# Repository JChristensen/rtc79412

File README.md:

# MCP78411/12 RTC Break-Out Board
https://github.com/JChristensen/rtc79412  
README file  
Jack Christensen  
Sep-2012

## License
  
This work is licensed under the [Creative Commons Attribution-ShareAlike 4.0 International License](https://creativecommons.org/licenses/by-sa/4.0/).

## Introduction
Break-out board for the Microchip MCP78411/12 Real-Time Clock.  

For an Arduino library that supports the MCP79412 RTC, see:
https://github.com/JChristensen/MCP79412RTC

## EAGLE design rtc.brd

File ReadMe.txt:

ReadMe file for MCP79412 Real-Time Clock Breakout Board v1.0
https://github.com/JChristensen/rtc79412
Jack Christensen Sep 2012

This work is licensed under the Creative Commons Attribution-ShareAlike 3.0
Unported License. To view a copy of this license, visit
http://creativecommons.org/licenses/by-sa/3.0/ or send a letter to Creative
Commons, 171 Second Street, Suite 300, San Francisco, California, 94105, USA.

================================================================================
This repository contains the following for the MCP79412 Real-Time Clock Breakout
Board:

Schematic
Eagle Files
Bill of materials (below)

For an Arduino library that supports the MCP79412 RTC, see:
https://github.com/JChristensen/MCP79412RTC

================================================================================
MCP79412 RTC Breakout Board
Bill of Materials

Part   Value                   Package   Comments
----   ---------------------   -------   ---------------------------------
B1     CR2016 battery holder             Linx Technologies BAT-HLD-002-SMT
C1     100nF                   C0805
C2     100pF                   C0805
C3     10pF                    C0805
C4     8.2pF                   C0805
D1     PMEG6002EJ              SOD323    NXP Low Vf Schottky Diode
R1     10K                     R0805
R2     2.2K                    R0805
R3     2.2K                    R0805
R4     1K                      R0805
U1     MCP79412-I/SN           SO08
Y1     32.768 kHz                        Citizen CM200C-32.768KDZB-UT

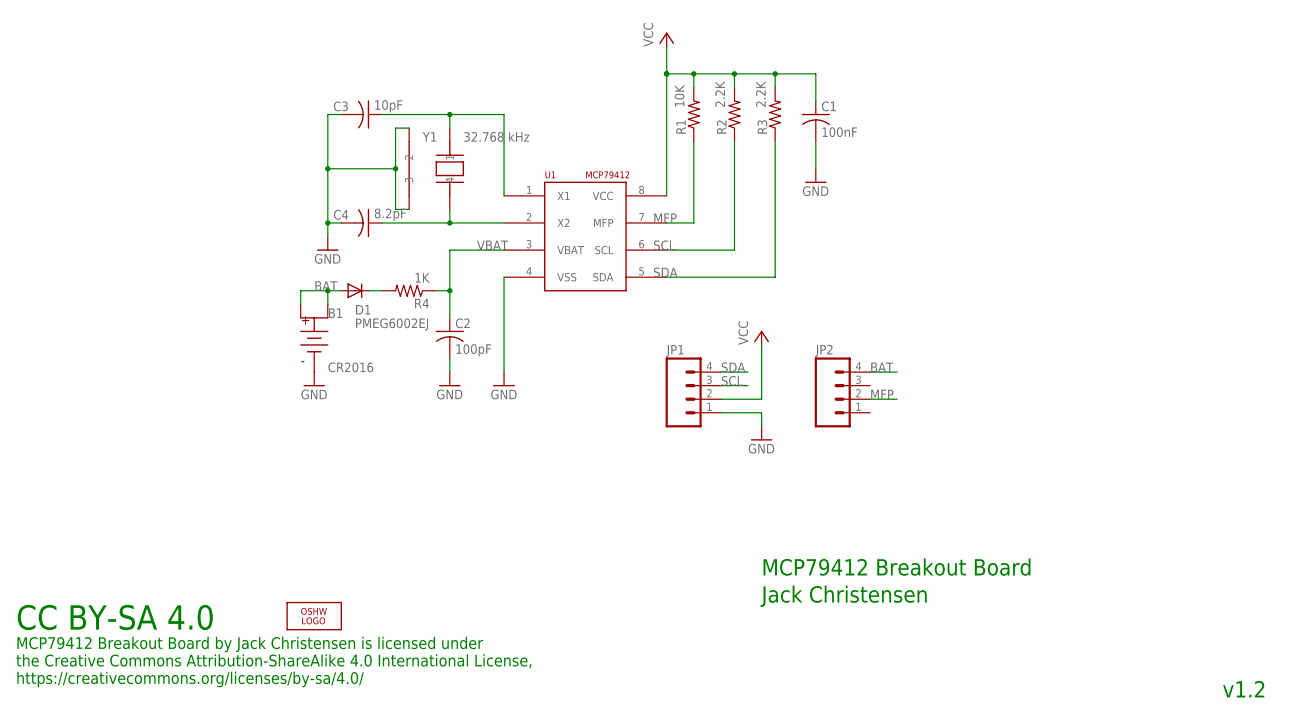
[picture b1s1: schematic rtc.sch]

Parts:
B1: CR2016; BAT-HLD-002-SMT
C1: 100nF; M0805
C2: 100pF; M0805
C3: 10pF; M0805
C4: 8.2pF; M0805
D1: PMEG6002EJ; SOD-323F-A
JP1, JP2: M04LOCK; 1X04_LOCK
LOGO2: OSHW_LOGO_8MILX0150-NT; OSHW_8X150_NOTEXT
R1: 10K; M0805
R2, R3: 2.2K; M0805
R4: 1K; M0805
U1: MCP79412; SO08
Y1: 32.768 kHz; CRYSTAL-CITIZEN-CM2XXC

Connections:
BAT: B1.POS1, B1.POS2, D1.A, JP2.4
GND: B1.NEG (B-), C1.2, C2.2, C3.2, C4.2, JP1.1, U1.4 (VSS), Y1.P$2 (2), Y1.P$3 (3)
MFP: JP2.2, R1.1, U1.7 (MFP)
unnamed: D1.K, R4.2
unnamed: C4.1, U1.2 (X2), Y1.P$4 (4)
unnamed: C3.1, U1.1 (X1), Y1.P$1 (1)
SCL: JP1.3, R2.1, U1.6 (SCL)
SDA: JP1.4, R3.1, U1.5 (SDA)
VBAT: C2.1, R4.1, U1.3 (VBAT)
VCC: C1.1, JP1.2, R1.2, R2.2, R3.2, U1.8 (VCC)

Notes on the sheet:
MCP79412 Breakout Board by Jack Christensen is licensed under the Creative Commons Attribution-ShareAlike 4.0 International License, https://creativecommons.org/licenses/by-sa/4.0/
CC BY-SA 4.0
MCP79412 Breakout Board
Jack Christensen
v1.2

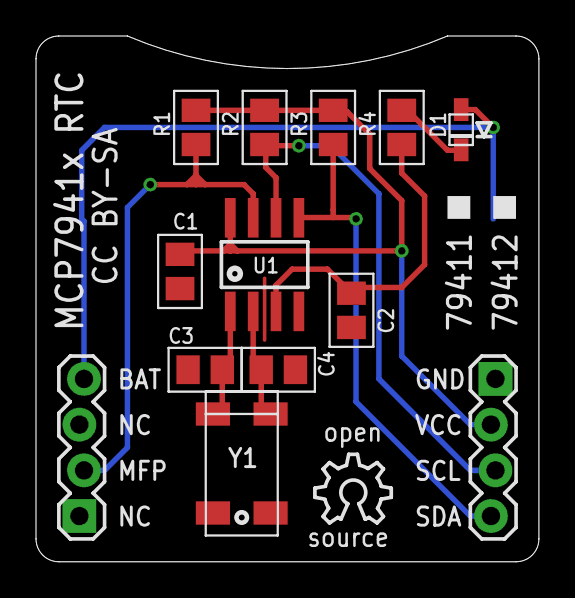
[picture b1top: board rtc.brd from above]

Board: 2 copper layers, 27.9 x 29.2 mm, 15 parts (1 on the bottom side), 10 nets.

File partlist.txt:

Partlist

Exported from rtc.sch at 12/7/21 7:40 PM

EAGLE Version 9.6.2 Copyright (c) 1988-2020 Autodesk, Inc.

Assembly variant: 

Part     Value          Device                 Package                Library  Sheet

B1       CR2016         COIN-CELL-2016-SMT     BAT-HLD-002-SMT        _jc      1
C1       100nF          C-USM0805              M0805                  _jc      1
C2       100pF          C-USM0805              M0805                  _jc      1
C3       10pF           C-USM0805              M0805                  _jc      1
C4       8.2pF          C-USM0805              M0805                  _jc      1
D1       PMEG6002EJ     DIODESOD-323F-A        SOD-323F-A             _jc      1
JP1                     M04LOCK                1X04_LOCK              SparkFun 1
JP2                     M04LOCK                1X04_LOCK              SparkFun 1
R1       10K            R-US_M0805             M0805                  _jc      1
R2       2.2K           R-US_M0805             M0805                  _jc      1
R3       2.2K           R-US_M0805             M0805                  _jc      1
R4       1K             R-US_M0805             M0805                  _jc      1
U1       MCP79412       MCP7941X-SOIC-8        SO08                   _jc      1
Y1       32.768 kHz     CRYSTAL-CITIZEN-CM2XXC CRYSTAL-CITIZEN-CM2XXC _jc      1

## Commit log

2012-07-31 v1.0 as sent to OSH Park
2012-09-15 v1.0
2012-09-26 v1.1 Larger pads for D1.
2012-10-04 Final layout as sent to fab.
2012-10-04 Add .gitignore file.
2013-07-21 Updated coin cell footprint, R and C footprints, OSHW logo.
2014-02-18 Add .gko to .gitignore.
2021-12-08 Update README, add LICENSE and other misc files. Regenerate Gerber files.

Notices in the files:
parts and their libraries:
SparkFun: Licensing: CC v3.0 Share-Alike You are welcome to use this library for commercial purposes.
